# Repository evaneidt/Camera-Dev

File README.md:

# Camera-Dev
Repo for camera dev board schematics, CAD, and code.

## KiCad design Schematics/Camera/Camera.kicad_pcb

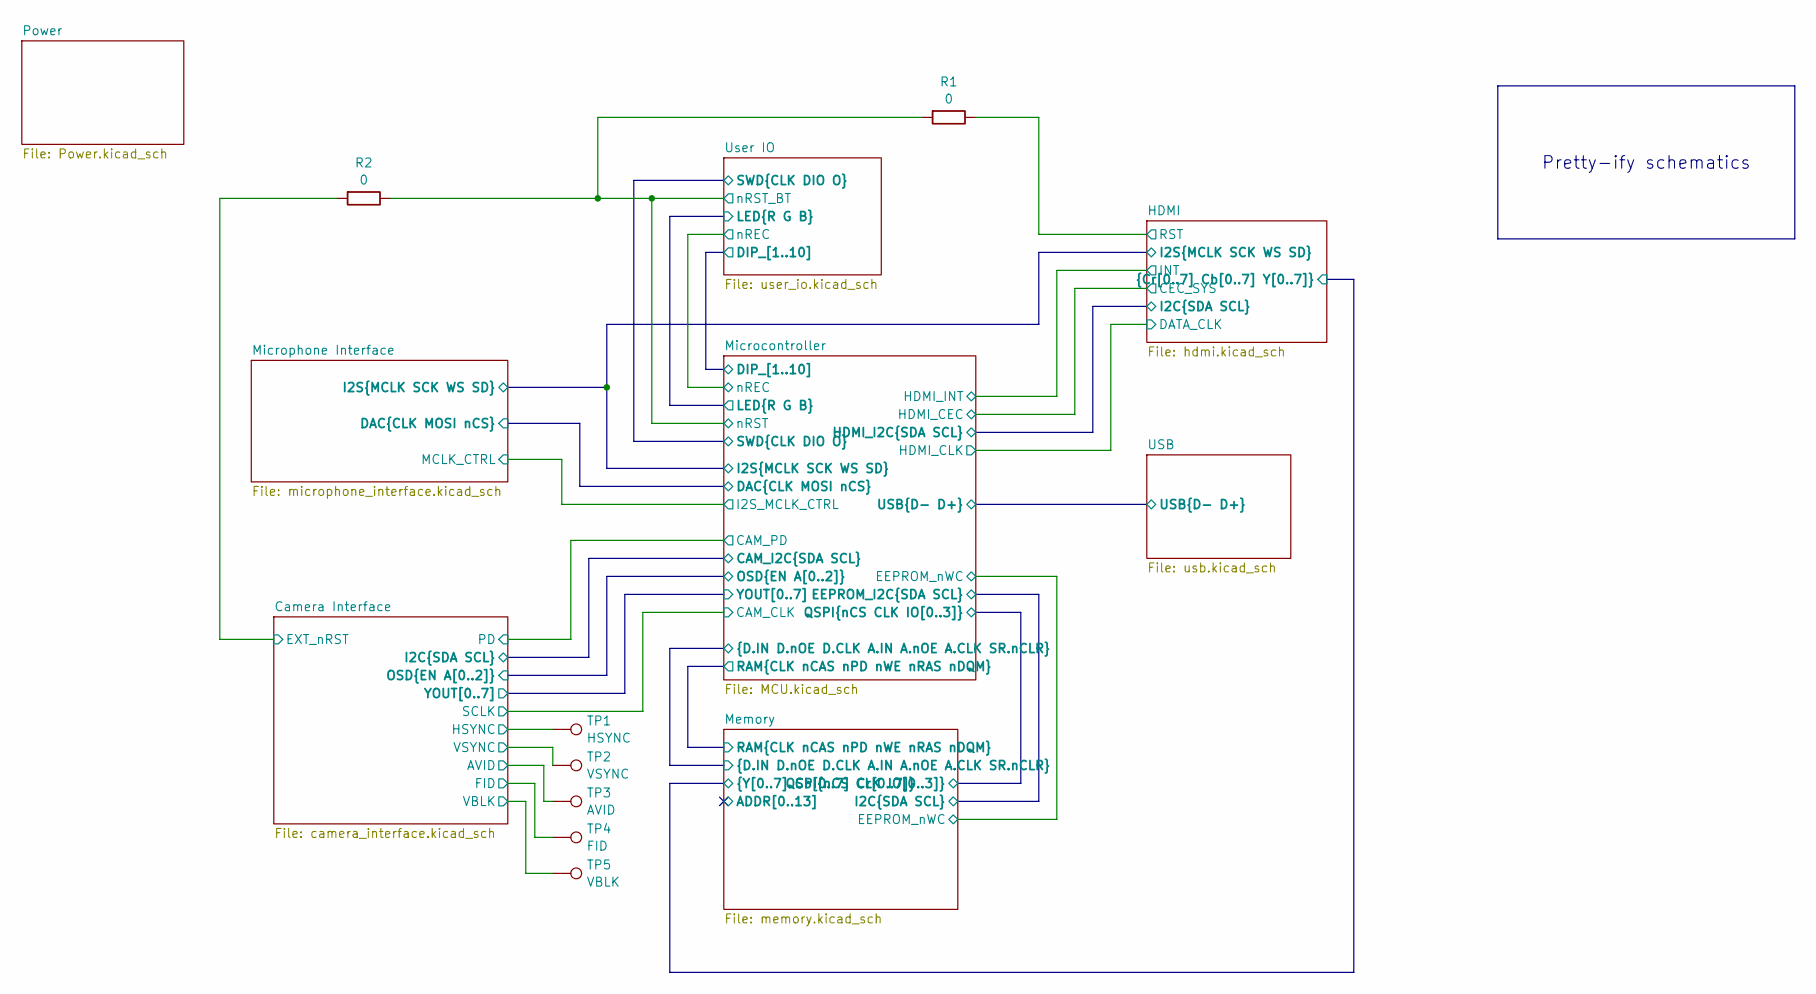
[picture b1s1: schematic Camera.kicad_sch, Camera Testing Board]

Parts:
R1, R2: 0; R_0603_1608Metric
TP1: HSYNC; TestPoint_Keystone_5000-5004_Miniature
TP2: VSYNC; TestPoint_Keystone_5000-5004_Miniature
TP3: AVID; TestPoint_Keystone_5000-5004_Miniature
TP4: FID; TestPoint_Keystone_5000-5004_Miniature
TP5: VBLK; TestPoint_Keystone_5000-5004_Miniature

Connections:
/Camera Interface/AVID: TP3.1; also elsewhere on the board
/Camera Interface/EXT_nRST: R2.1; also elsewhere on the board
/Camera Interface/FID: TP4.1; also elsewhere on the board
/Camera Interface/HSYNC: TP1.1; also elsewhere on the board
/Camera Interface/VBLK: TP5.1; also elsewhere on the board
/Camera Interface/VSYNC: TP2.1; also elsewhere on the board
/HDMI/RST: R1.2; also elsewhere on the board
/User IO/nRST_BT: R1.1, R2.2; also elsewhere on the board

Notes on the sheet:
Pretty-ify schematics

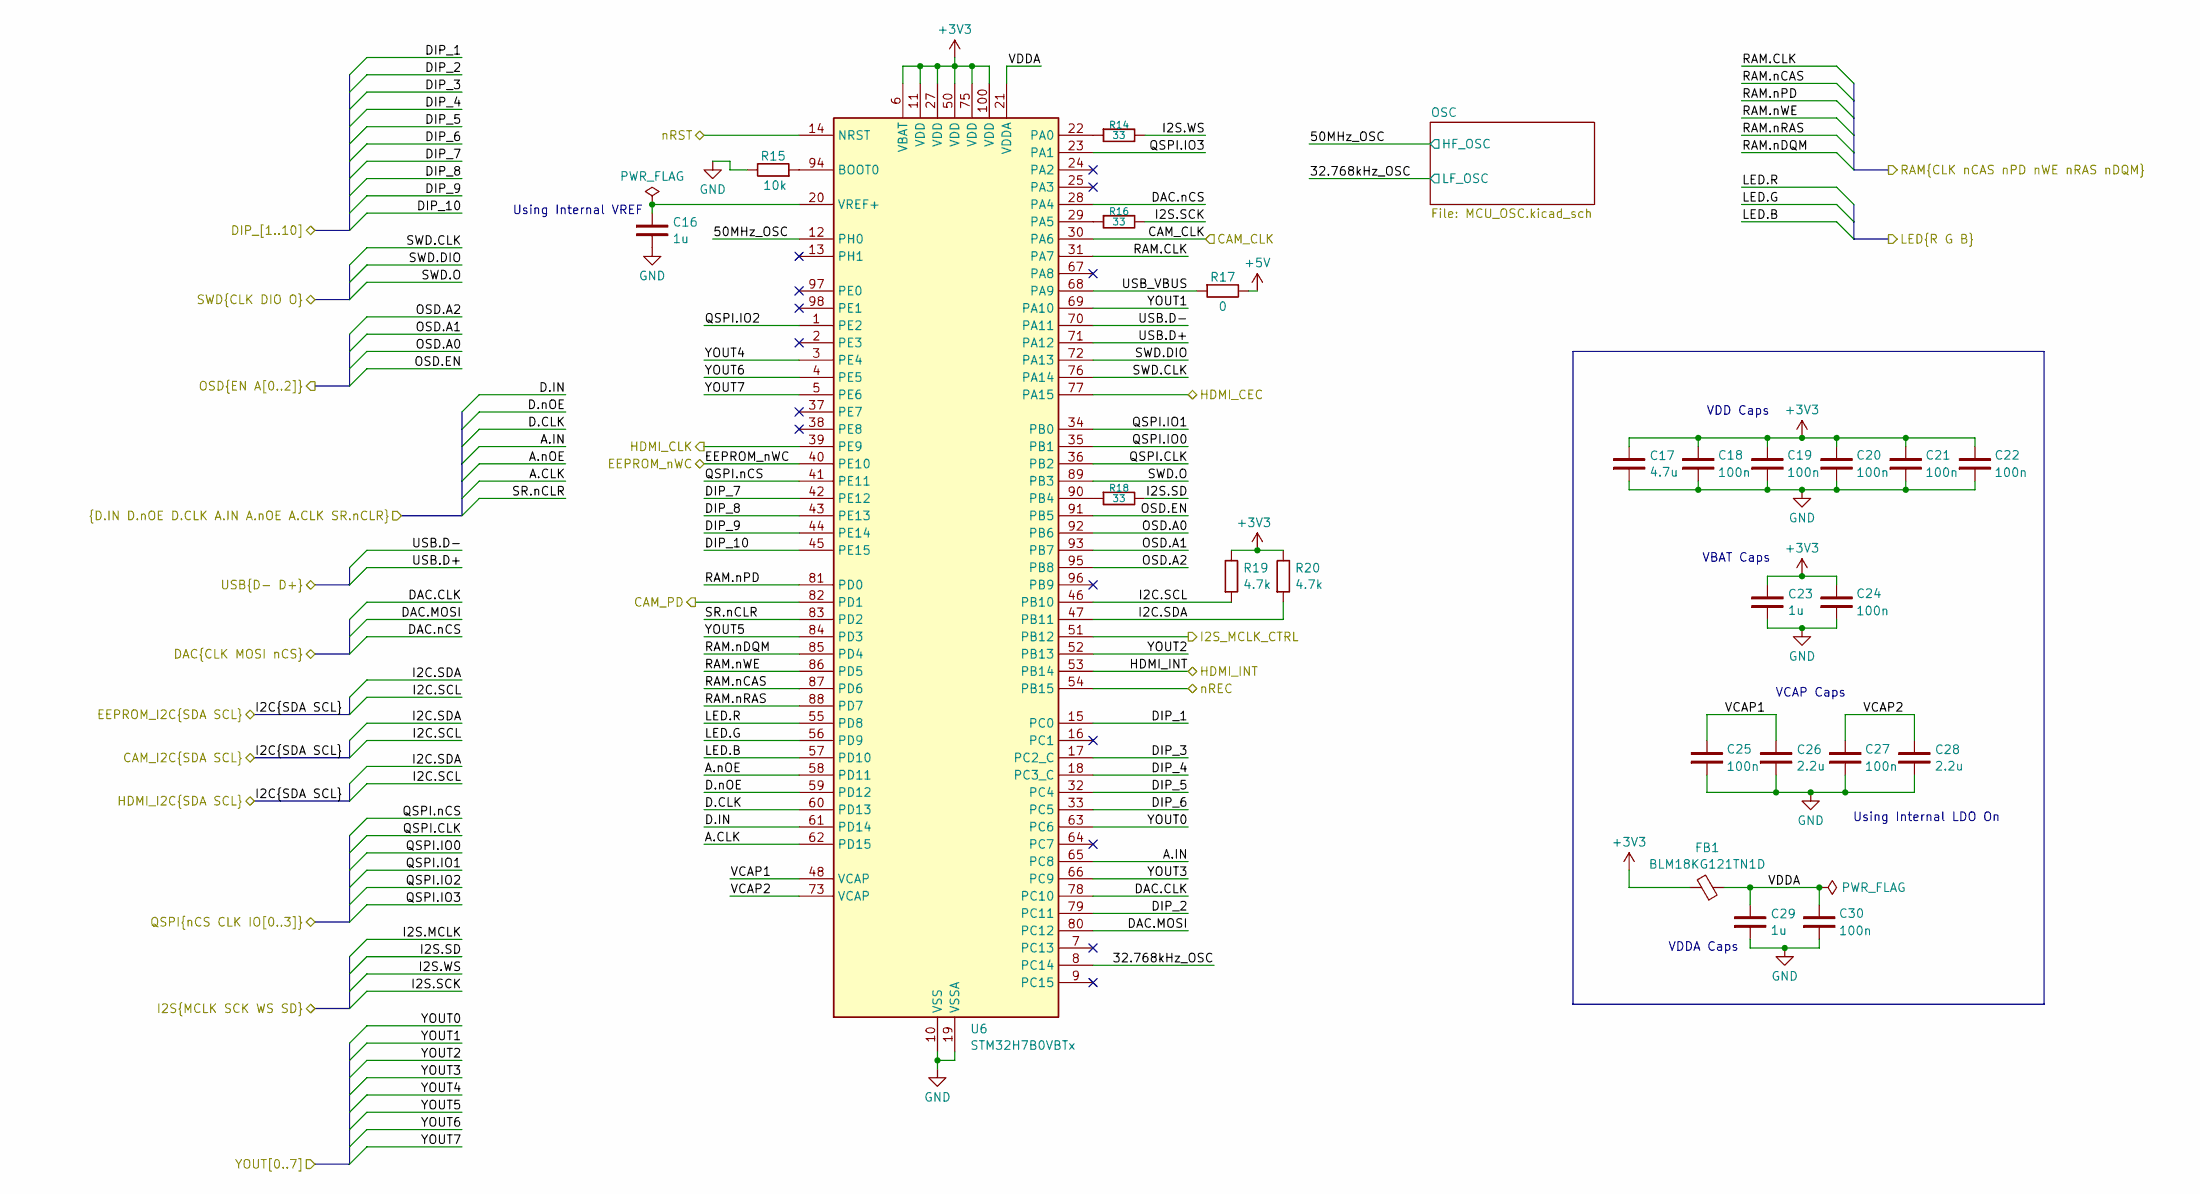
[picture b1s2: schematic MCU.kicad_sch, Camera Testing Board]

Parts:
C16, C23, C29: 1u; C_0603_1608Metric
C17: 4.7u; C_0603_1608Metric
C18, C19, C20, C21, C22, C24, C25, C27, C30: 100n; C_0603_1608Metric
C26, C28: 2.2u; C_0603_1608Metric
FB1: BLM18KG121TN1D; L_0603_1608Metric
R14, R16, R18: 33; R_0402_1005Metric
R15: 10k; R_0603_1608Metric
R17: 0; R_0603_1608Metric
R19, R20: 4.7k; R_0603_1608Metric
U6: STM32H7B0VBTx; LQFP-100_14x14mm_P0.5mm

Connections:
+3V3: C17.2, C18.2, C19.2, C20.2, C21.2, C22.2, C23.2, C24.2, FB1.2, R19.2, R20.2, U6.6 (VBAT), U6.11 (VDD), U6.27 (VDD), U6.50 (VDD), U6.75 (VDD), U6.100 (VDD); also elsewhere on the board
+5V: R17.2; also elsewhere on the board
/Camera Interface/OSD.A0: U6.92 (PB6); also elsewhere on the board
/Camera Interface/OSD.A1: U6.93 (PB7); also elsewhere on the board
/Camera Interface/OSD.A2: U6.95 (PB8); also elsewhere on the board
/Camera Interface/OSD.EN: U6.91 (PB5); also elsewhere on the board
/Camera Interface/PD: U6.82 (PD1); also elsewhere on the board
/Camera Interface/SCLK: U6.30 (PA6); also elsewhere on the board
/Camera Interface/YOUT0: U6.63 (PC6); also elsewhere on the board
/Camera Interface/YOUT1: U6.69 (PA10); also elsewhere on the board
/Camera Interface/YOUT2: U6.52 (PB13); also elsewhere on the board
/Camera Interface/YOUT3: U6.66 (PC9); also elsewhere on the board
/Camera Interface/YOUT4: U6.3 (PE4); also elsewhere on the board
/Camera Interface/YOUT5: U6.84 (PD3); also elsewhere on the board
/Camera Interface/YOUT6: U6.4 (PE5); also elsewhere on the board
/Camera Interface/YOUT7: U6.5 (PE6); also elsewhere on the board
/HDMI/CEC_SYS: U6.77 (PA15); also elsewhere on the board
/HDMI/DATA_CLK: U6.39 (PE9); also elsewhere on the board
/HDMI/I2C.SCL: R19.1, U6.46 (PB10); also elsewhere on the board
/HDMI/I2C.SDA: R20.1, U6.47 (PB11); also elsewhere on the board
/HDMI/I2S.SCK: R16.2; also elsewhere on the board
/HDMI/I2S.SD: R18.2; also elsewhere on the board
/HDMI/I2S.WS: R14.2; also elsewhere on the board
/HDMI/INT: U6.53 (PB14); also elsewhere on the board
/Memory/A.CLK: U6.62 (PD15); also elsewhere on the board
/Memory/A.IN: U6.65 (PC8); also elsewhere on the board
/Memory/A.nOE: U6.58 (PD11); also elsewhere on the board
/Memory/D.CLK: U6.60 (PD13); also elsewhere on the board
/Memory/D.IN: U6.61 (PD14); also elsewhere on the board
/Memory/D.nOE: U6.59 (PD12); also elsewhere on the board
/Memory/EEPROM_nWC: U6.40 (PE10); also elsewhere on the board
/Memory/QSPI.CLK: U6.36 (PB2); also elsewhere on the board
/Memory/QSPI.IO0: U6.35 (PB1); also elsewhere on the board
/Memory/QSPI.IO1: U6.34 (PB0); also elsewhere on the board
/Memory/QSPI.IO2: U6.1 (PE2); also elsewhere on the board
/Memory/QSPI.IO3: U6.23 (PA1); also elsewhere on the board
/Memory/QSPI.nCS: U6.41 (PE11); also elsewhere on the board
/Memory/RAM.CLK: U6.31 (PA7); also elsewhere on the board
/Memory/RAM.nCAS: U6.87 (PD6); also elsewhere on the board
/Memory/RAM.nDQM: U6.85 (PD4); also elsewhere on the board
/Memory/RAM.nPD: U6.81 (PD0); also elsewhere on the board
/Memory/RAM.nRAS: U6.88 (PD7); also elsewhere on the board
/Memory/RAM.nWE: U6.86 (PD5); also elsewhere on the board
/Memory/SR.nCLR: U6.83 (PD2); also elsewhere on the board
/Microcontroller/32.768kHz_OSC: U6.8 (PC14); also elsewhere on the board
/Microcontroller/50MHz_OSC: U6.12 (PH0); also elsewhere on the board
/Microcontroller/DAC.CLK: U6.78 (PC10); also elsewhere on the board
/Microcontroller/DAC.MOSI: U6.80 (PC12); also elsewhere on the board
/Microcontroller/DAC.nCS: U6.28 (PA4); also elsewhere on the board
/Microcontroller/DIP_1: U6.15 (PC0)
/Microcontroller/DIP_2: U6.79 (PC11)
/Microcontroller/DIP_3: U6.17 (PC2_C)
/Microcontroller/DIP_4: U6.18 (PC3_C)
/Microcontroller/DIP_5: U6.32 (PC4)
/Microcontroller/DIP_6: U6.33 (PC5)
/Microcontroller/DIP_7: U6.42 (PE12)
/Microcontroller/DIP_8: U6.43 (PE13)
/Microcontroller/DIP_9: U6.44 (PE14)
/Microcontroller/DIP_10: U6.45 (PE15)
/Microcontroller/LED.B: U6.57 (PD10); also elsewhere on the board
/Microcontroller/LED.G: U6.56 (PD9); also elsewhere on the board
/Microcontroller/LED.R: U6.55 (PD8); also elsewhere on the board
/Microcontroller/SWD.CLK: U6.76 (PA14); also elsewhere on the board
/Microcontroller/SWD.DIO: U6.72 (PA13); also elsewhere on the board
/Microcontroller/SWD.O: U6.89 (PB3); also elsewhere on the board
/Microcontroller/USB.D+: U6.71 (PA12); also elsewhere on the board
/Microcontroller/USB.D-: U6.70 (PA11); also elsewhere on the board
/Microcontroller/USB_VBUS: R17.1, U6.68 (PA9)
/Microcontroller/VCAP1: C25.2, C26.2, U6.48 (VCAP)
/Microcontroller/VCAP2: C27.2, C28.2, U6.73 (VCAP)
/Microcontroller/VDDA: C29.2, C30.2, FB1.1, U6.21 (VDDA)
/Microcontroller/nREC: U6.54 (PB15); also elsewhere on the board
/Microphone Interface/Microphone Clocks/CTRL: U6.51 (PB12); also elsewhere on the board
/User IO/nRST_BT: U6.14 (NRST); also elsewhere on the board
GND: C16.1, C17.1, C18.1, C19.1, C20.1, C21.1, C22.1, C23.1, C24.1, C25.1, C26.1, C27.1, C28.1, C29.1, C30.1, R15.2, U6.10 (VSS), U6.19 (VSSA), U6.26 (VSS), U6.49 (VSS), U6.74 (VSS), U6.99 (VSS); also elsewhere on the board
unnamed: R15.1, U6.94 (BOOT0)
unnamed: R14.1, U6.22 (PA0)
unnamed: R16.1, U6.29 (PA5)
unnamed: R18.1, U6.90 (PB4)
unnamed: C16.2, U6.20 (VREF+)

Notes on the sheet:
Using Internal LDO On
VDDA Caps
Using Internal VREF
VBAT Caps
VCAP Caps
VDD Caps

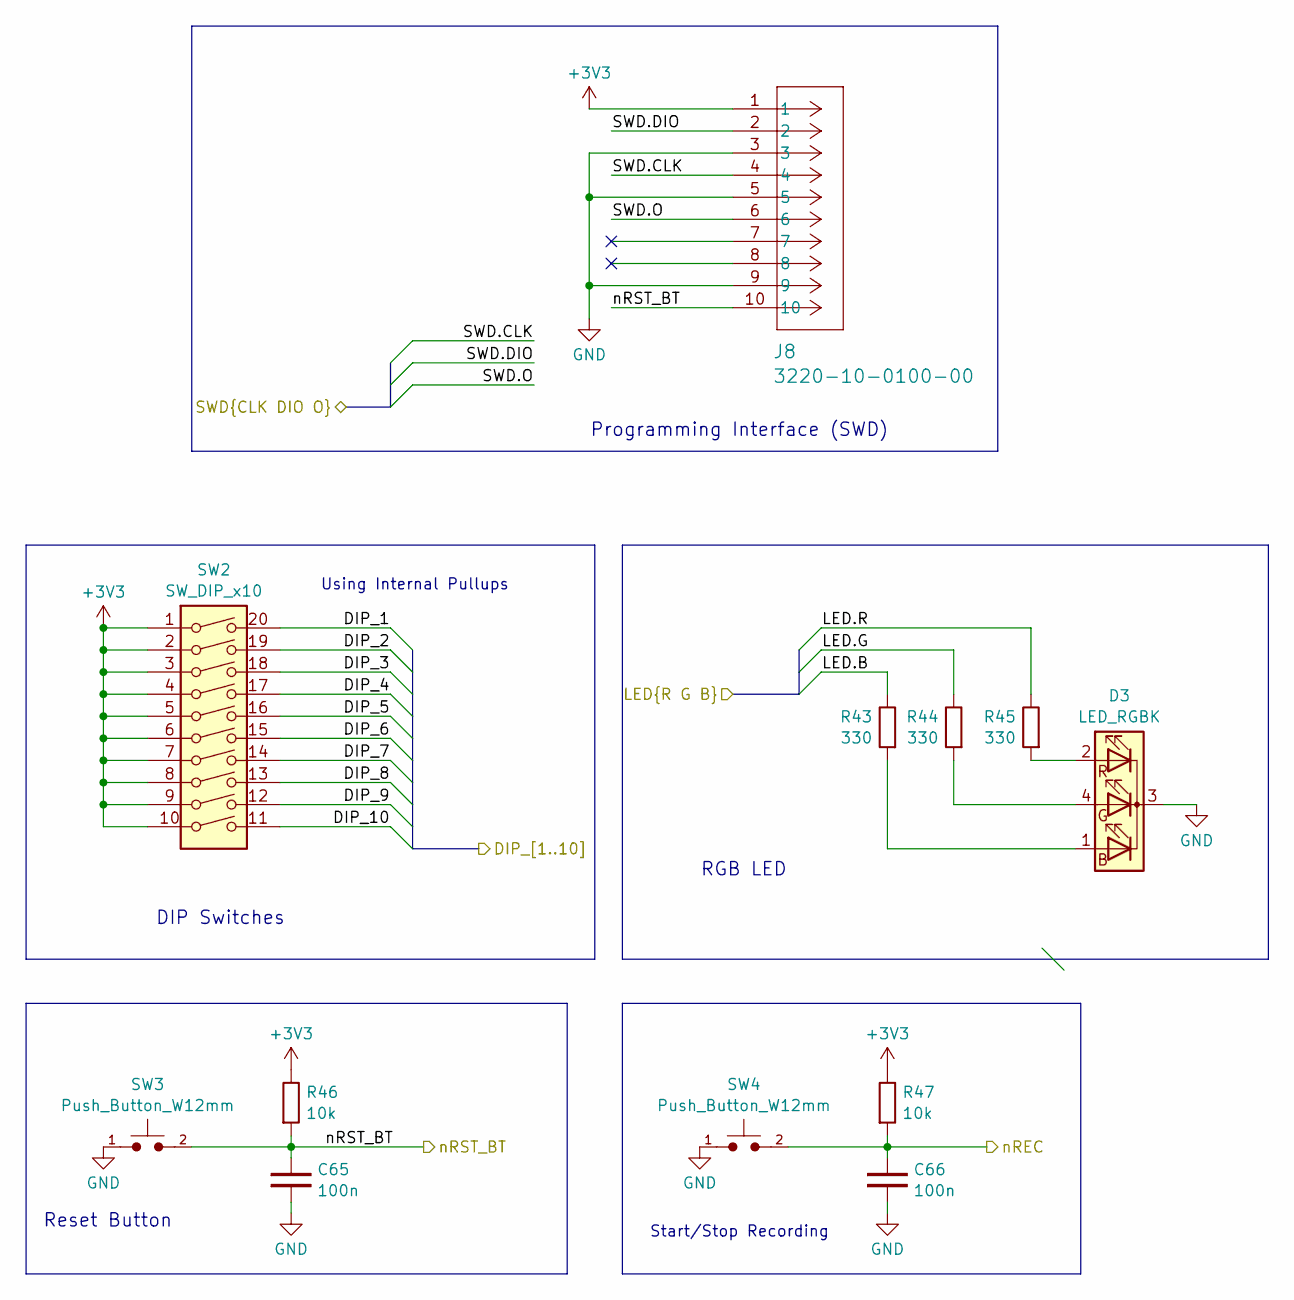
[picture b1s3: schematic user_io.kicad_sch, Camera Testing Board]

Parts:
C65, C66: 100n; C_0603_1608Metric
D3: LED_RGBK; LED_D5.0mm-4_RGB
J8: 3220-10-0100-00; CONN_3220-10-0100-00_CNC
R43, R44, R45: 330; R_0603_1608Metric
R46, R47: 10k; R_0603_1608Metric
SW2: SW_DIP_x10; DIP-20_W7.62mm
SW3, SW4: Push_Button_W12mm; SW_Push_1P1T_NO_CK_KSC7xxJ

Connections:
+3V3: J8.1, R46.2, R47.2, SW2.1, SW2.2, SW2.3, SW2.4, SW2.5, SW2.6, SW2.7, SW2.8, SW2.9, SW2.10; also elsewhere on the board
/Microcontroller/LED.B: R43.2; also elsewhere on the board
/Microcontroller/LED.G: R44.2; also elsewhere on the board
/Microcontroller/LED.R: R45.2; also elsewhere on the board
/Microcontroller/SWD.CLK: J8.4; also elsewhere on the board
/Microcontroller/SWD.DIO: J8.2; also elsewhere on the board
/Microcontroller/SWD.O: J8.6; also elsewhere on the board
/Microcontroller/nREC: C66.2, R47.1, SW4.2; also elsewhere on the board
/User IO/nRST_BT: C65.2, J8.10, R46.1, SW3.2; also elsewhere on the board
GND: C65.1, C66.1, D3.3 (K), J8.3, J8.5, J8.9, SW3.1, SW4.1; also elsewhere on the board
unnamed: D3.1 (BA), R43.1
unnamed: D3.4 (GA), R44.1
unnamed: D3.2 (RA), R45.1

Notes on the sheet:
Using Internal Pullups
DIP Switches
Programming Interface (SWD)
Start/Stop Recording
Reset Button
RGB LED

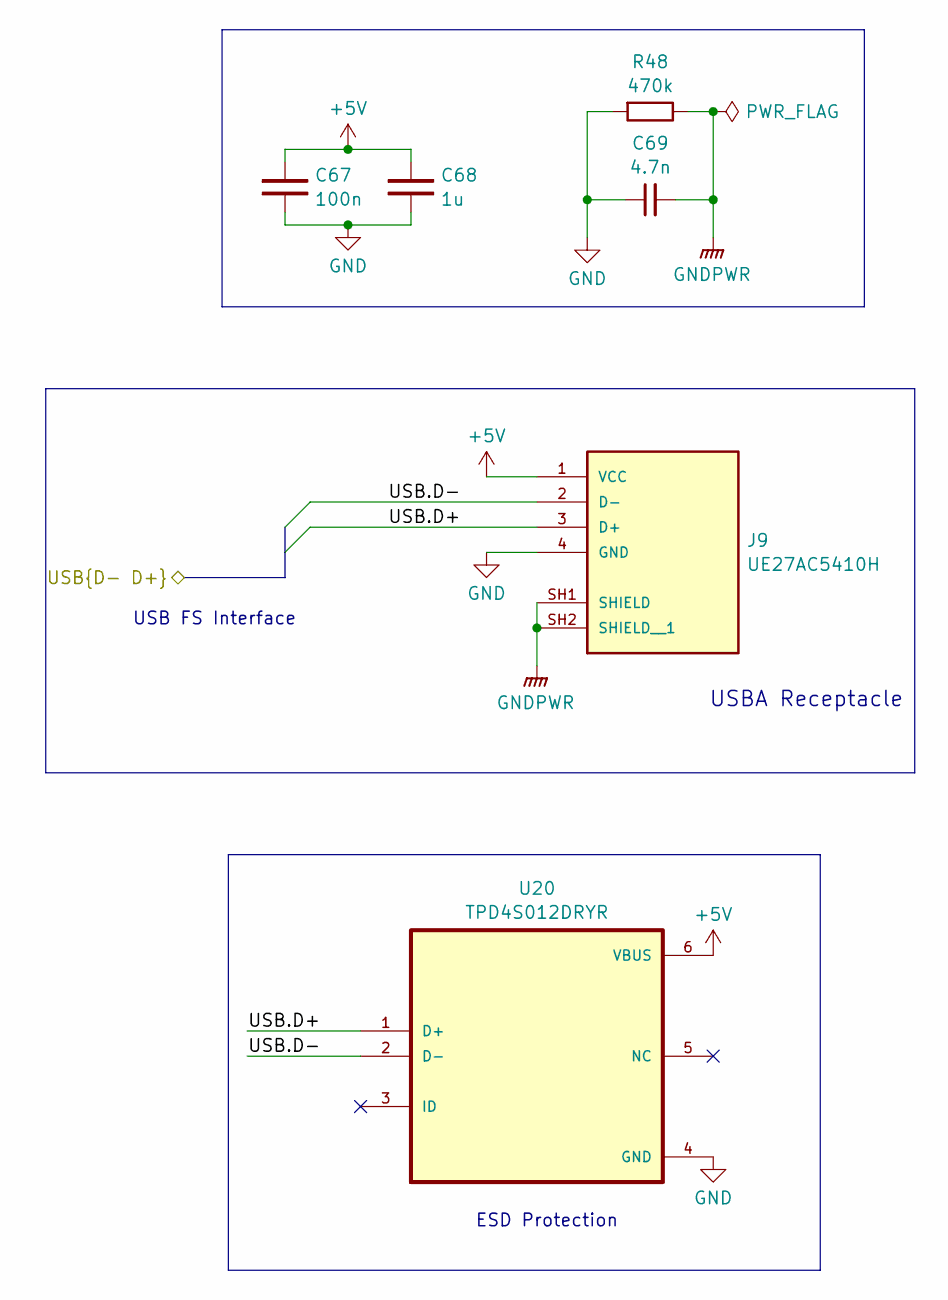
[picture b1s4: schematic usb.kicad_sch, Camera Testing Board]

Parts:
C67: 100n; C_0603_1608Metric
C68: 1u; C_0603_1608Metric
C69: 4.7n; C_0603_1608Metric
J9: UE27AC5410H; AMPHENOL_UE27AC5410H; PARTREV G
R48: 470k; R_0603_1608Metric
U20: TPD4S012DRYR; PSON50P145X100X60-6N

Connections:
+5V: C67.2, C68.2, J9.1 (VCC), U20.6 (VBUS); also elsewhere on the board
/Microcontroller/USB.D+: J9.3 (D+), U20.1 (D+); also elsewhere on the board
/Microcontroller/USB.D-: J9.2 (D-), U20.2 (D-); also elsewhere on the board
GND: C67.1, C68.1, C69.1, J9.4 (GND), R48.1, U20.4 (GND); also elsewhere on the board
GNDPWR: C69.2, J9.SH1 (SHIELD), J9.SH2 (SHIELD__1), R48.2; also elsewhere on the board

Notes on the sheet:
USB FS Interface
ESD Protection
USBA Receptacle

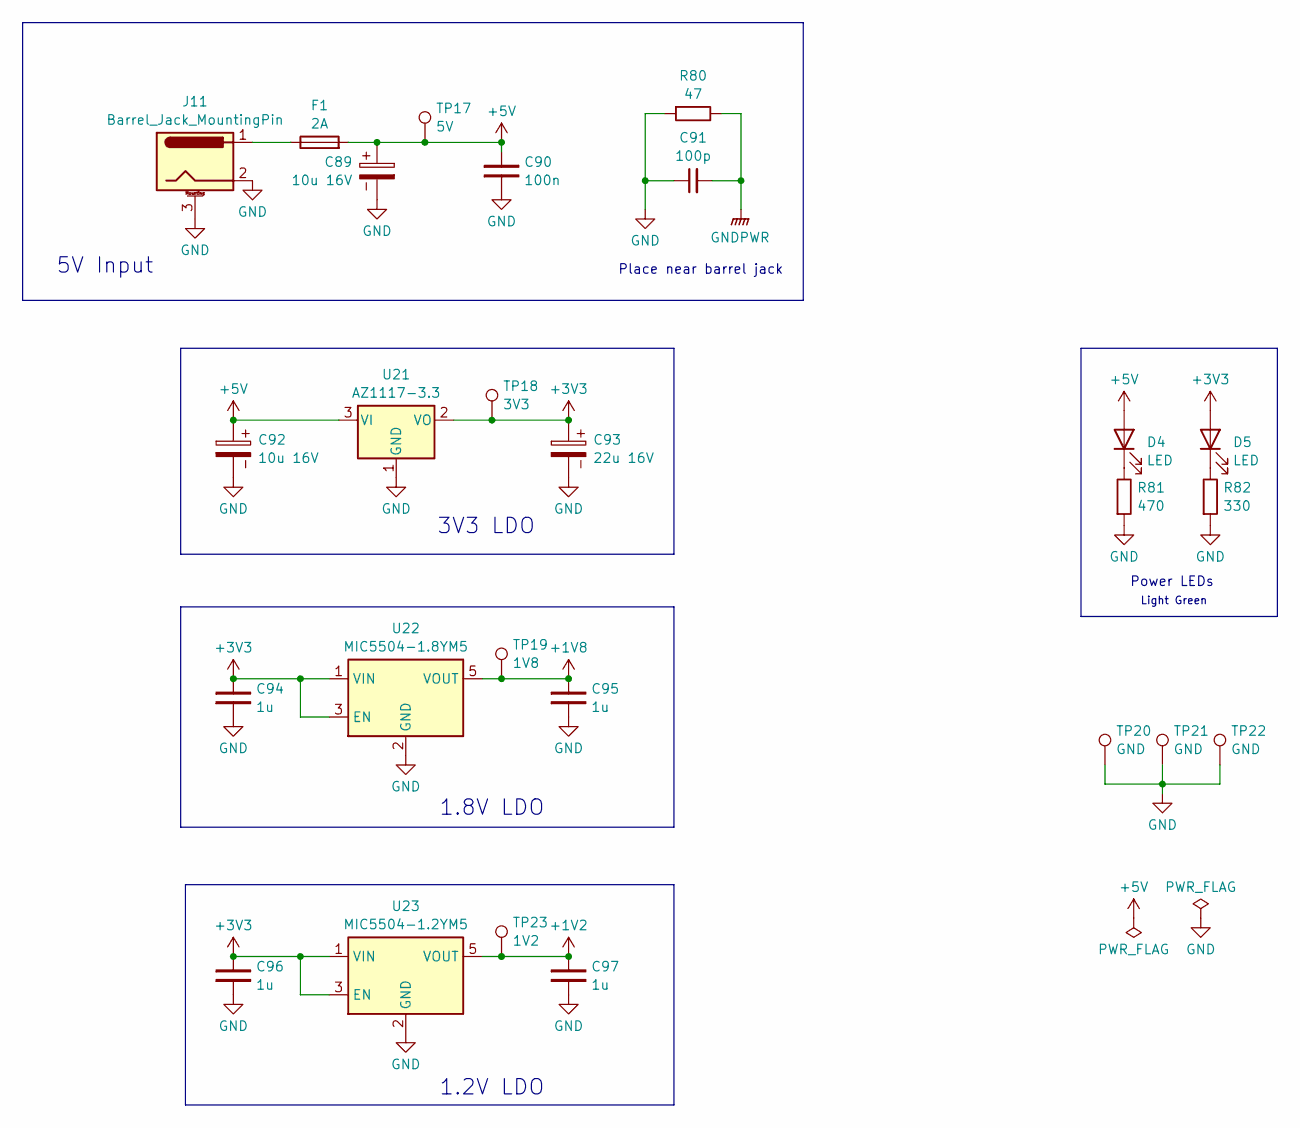
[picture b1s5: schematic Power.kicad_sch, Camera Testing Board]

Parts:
C89, C92: 10u 16V; CP_EIA-3216-18_Kemet-A
C90: 100n; C_0603_1608Metric
C91: 100p; C_0402_1005Metric
C93: 22u 16V; CP_EIA-3528-21_Kemet-B
C94, C95, C96, C97: 1u; C_0603_1608Metric
D4, D5: LED; LED_0603_1608Metric
F1: 2A; Fuse_0603_1608Metric_Pad1.05x0.95mm_HandSolder
J11: Barrel_Jack_MountingPin; BarrelJack_CUI_PJ-036AH-SMT_Horizontal
R80: 47; R_0603_1608Metric
R81: 470; R_0603_1608Metric
R82: 330; R_0603_1608Metric
TP17: 5V; TestPoint_Keystone_5000-5004_Miniature
TP18: 3V3; TestPoint_Keystone_5000-5004_Miniature
TP19: 1V8; TestPoint_Keystone_5000-5004_Miniature
TP20, TP21, TP22: GND; TestPoint_Keystone_5010-5014_Multipurpose
TP23: 1V2; TestPoint_Keystone_5000-5004_Miniature
U21: AZ1117-3.3; SOT-223-3_TabPin2
U22: MIC5504-1.8YM5; SOT-23-5
U23: MIC5504-1.2YM5; SOT-23-5

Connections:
+1V2: C97.2, TP23.1, U23.5 (VOUT); also elsewhere on the board
+1V8: C95.2, TP19.1, U22.5 (VOUT); also elsewhere on the board
+3V3: C93.1, C94.2, C96.2, D5.2 (A), TP18.1, U21.2 (VO), U22.1 (VIN), U22.3 (EN), U23.1 (VIN), U23.3 (EN); also elsewhere on the board
+5V: C89.1, C90.2, C92.1, D4.2 (A), F1.2, TP17.1, U21.3 (VI); also elsewhere on the board
GND: C89.2, C90.1, C91.1, C92.2, C93.2, C94.1, C95.1, C96.1, C97.1, J11.2, J11.3 (MountPin), R80.1, R81.1, R82.1, TP20.1, TP21.1, TP22.1, U21.1 (GND), U22.2 (GND), U23.2 (GND); also elsewhere on the board
GNDPWR: C91.2, R80.2; also elsewhere on the board
unnamed: D4.1 (K), R81.2
unnamed: D5.1 (K), R82.2
unnamed: F1.1, J11.1

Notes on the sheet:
Place near barrel jack
1.8V LDO
1.2V LDO
Power LEDs
3V3 LDO
Light Green
5V Input

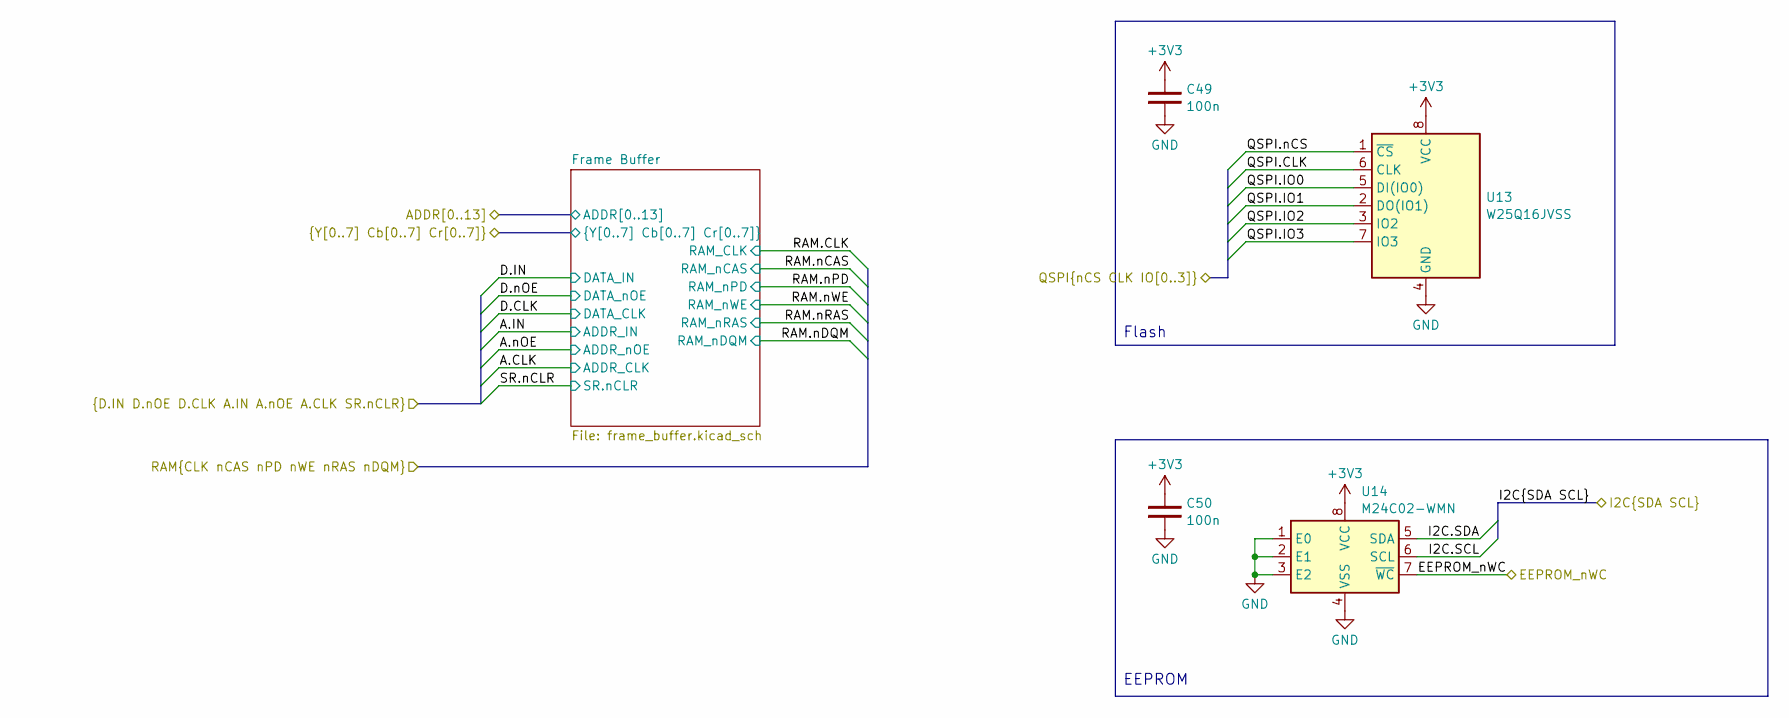
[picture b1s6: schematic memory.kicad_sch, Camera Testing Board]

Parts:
C49, C50: 100n; C_0603_1608Metric
U13: W25Q16JVSS; SOIC-8_5.23x5.23mm_P1.27mm
U14: M24C02-WMN; SOIC-8_3.9x4.9mm_P1.27mm

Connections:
+3V3: C49.2, C50.2, U13.8 (VCC), U14.8 (VCC); also elsewhere on the board
/HDMI/I2C.SCL: U14.6 (SCL); also elsewhere on the board
/HDMI/I2C.SDA: U14.5 (SDA); also elsewhere on the board
/Memory/EEPROM_nWC: U14.7 (~WC); also elsewhere on the board
/Memory/QSPI.CLK: U13.6 (CLK); also elsewhere on the board
/Memory/QSPI.IO0: U13.5 (DI(IO0)); also elsewhere on the board
/Memory/QSPI.IO1: U13.2 (DO(IO1)); also elsewhere on the board
/Memory/QSPI.IO2: U13.3 (IO2); also elsewhere on the board
/Memory/QSPI.IO3: U13.7 (IO3); also elsewhere on the board
/Memory/QSPI.nCS: U13.1 (~CS); also elsewhere on the board
GND: C49.1, C50.1, U13.4 (GND), U14.1 (E0), U14.2 (E1), U14.3 (E2), U14.4 (VSS); also elsewhere on the board

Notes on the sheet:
Flash
EEPROM

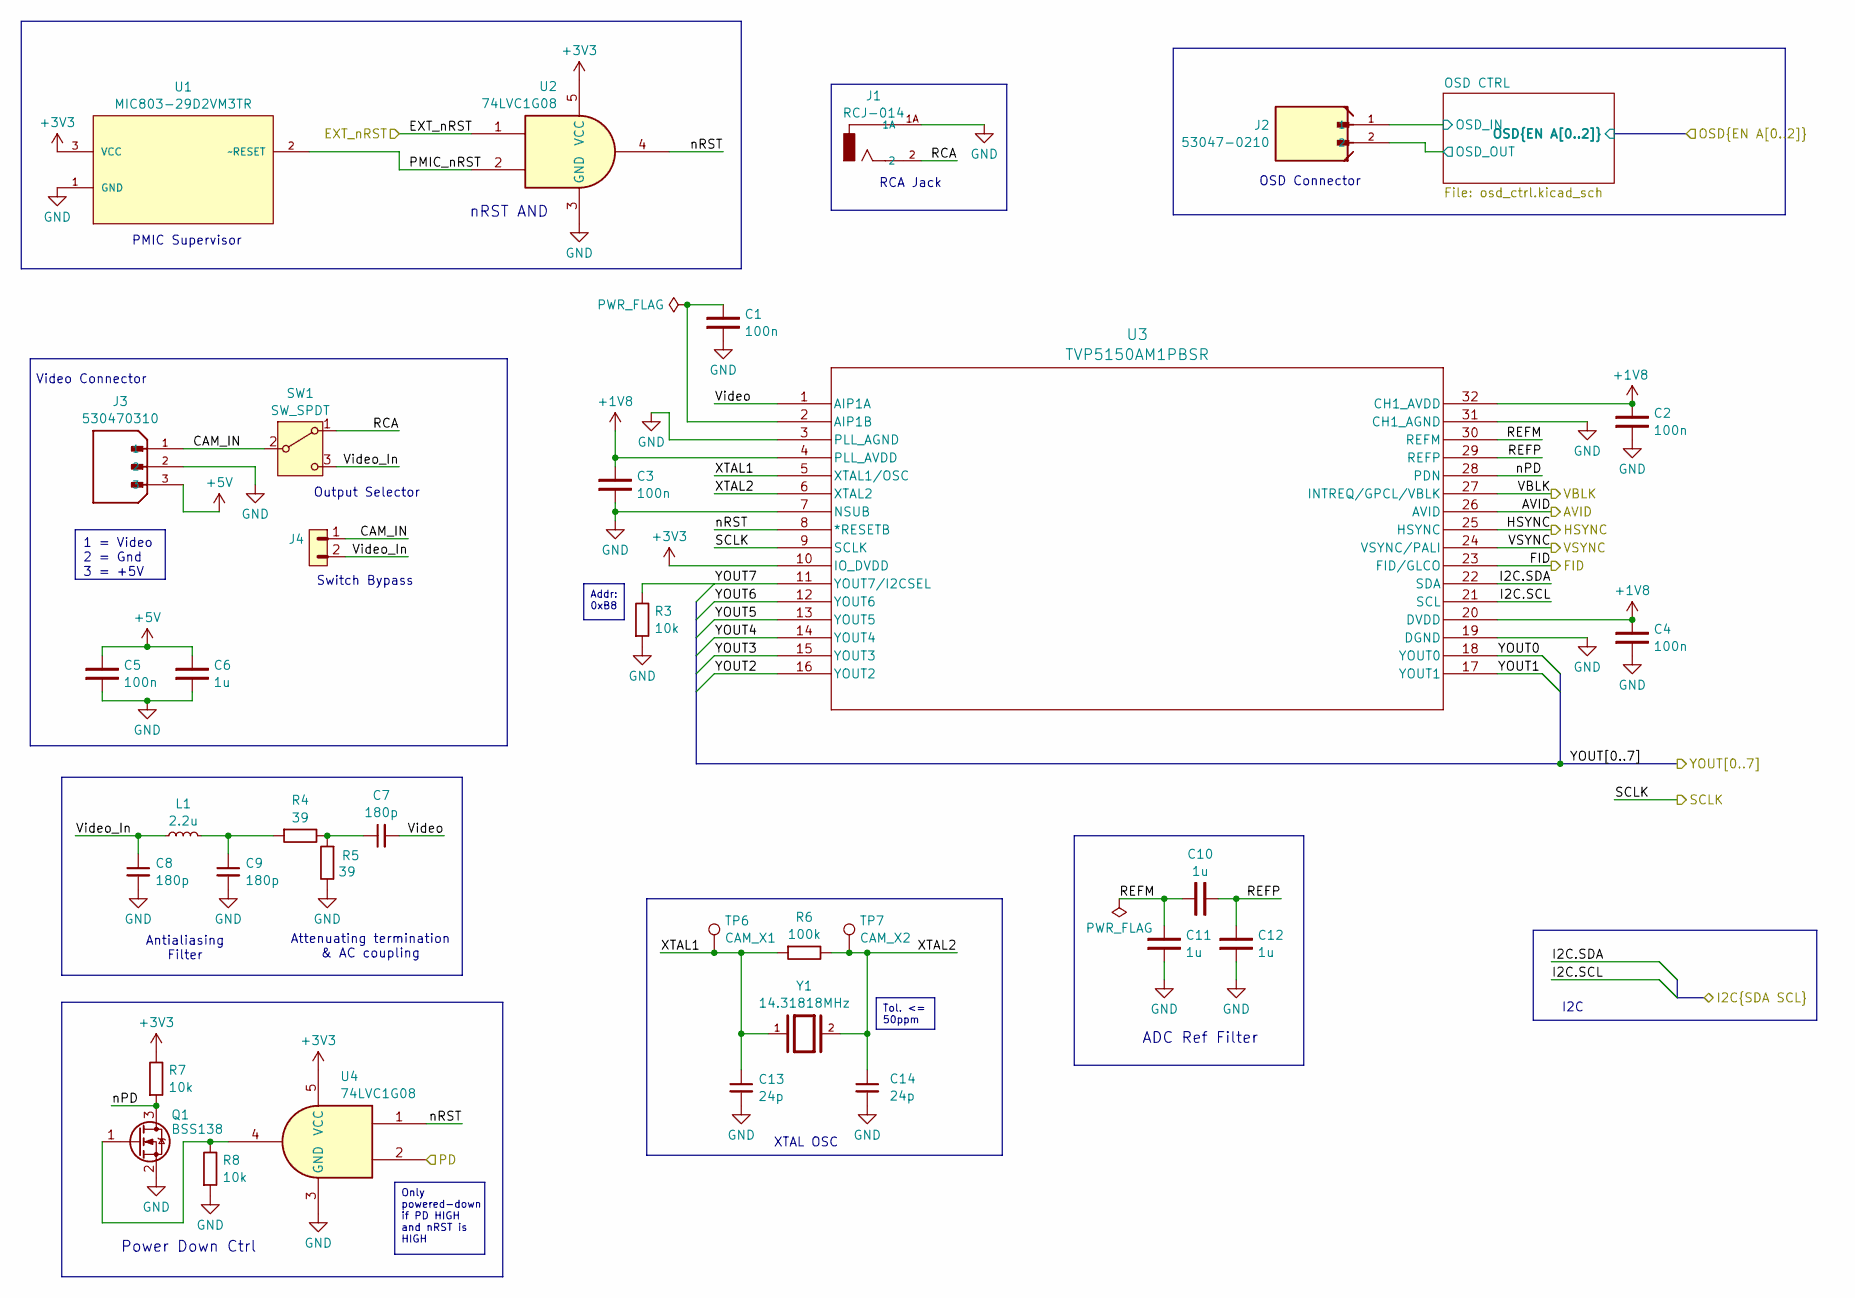
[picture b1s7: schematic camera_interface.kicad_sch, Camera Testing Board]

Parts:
C1, C2, C3, C4, C5: 100n; C_0603_1608Metric
C6, C10, C11, C12: 1u; C_0603_1608Metric
C7, C8, C9: 180p; C_0402_1005Metric
C13, C14: 24p; C_0402_1005Metric
J1: RCJ-014; CUI_RCJ-014; PART_REV B
J2: 53047-0210; Molex_PicoBlade_53047-0210_1x02_P1.25mm_Vertical; PARTREV 04/19/2022
J3: 530470310; MOLEX_530470310; PARTREV A
J4: PINHD_1x2_Male; PinHeader_1x02_P2.54mm_Vertical
L1: 2.2u; L_1008_2520Metric
Q1: BSS138; SOT-23
R3, R7, R8: 10k; R_0603_1608Metric
R4, R5: 39; R_0603_1608Metric
R6: 100k; R_0603_1608Metric
SW1: SW_SPDT; SW_Slide_SPDT_Straight_CK_OS102011MS2Q
TP6: CAM_X1; TestPoint_Keystone_5000-5004_Miniature
TP7: CAM_X2; TestPoint_Keystone_5000-5004_Miniature
U1: MIC803-29D2VM3TR; SOT95P232X110-3N; MPN MIC803-29D2VM3TR
U2, U4: 74LVC1G08; SOT-23-5
U3: TVP5150AM1PBSR; PBS32
Y1: 14.31818MHz; XTAL_ABLS2-14.31818MHZ-D4Y-T; PARTREV 11.15.2016

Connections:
+1V8: C2.2, C3.2, C4.2, U3.4 (PLL_AVDD), U3.20 (DVDD), U3.32 (CH1_AVDD); also elsewhere on the board
+3V3: R7.2, U1.3 (VCC), U2.5 (VCC), U3.10 (IO_DVDD), U4.5 (VCC); also elsewhere on the board
+5V: C5.2, C6.2, J3.3; also elsewhere on the board
/Camera Interface/AVID: U3.26 (AVID); also elsewhere on the board
/Camera Interface/CAM_IN: J3.1, J4.1, SW1.2 (B)
/Camera Interface/EXT_nRST: U2.1; also elsewhere on the board
/Camera Interface/FID: U3.23 (FID/GLCO); also elsewhere on the board
/Camera Interface/HSYNC: U3.25 (HSYNC); also elsewhere on the board
/Camera Interface/OSD CTRL/OSD_IN: J2.1; also elsewhere on the board
/Camera Interface/OSD CTRL/OSD_OUT: J2.2; also elsewhere on the board
/Camera Interface/PD: U4.2; also elsewhere on the board
/Camera Interface/PMIC_nRST: U1.2 (~RESET), U2.2
/Camera Interface/RCA: J1.2, SW1.1 (A)
/Camera Interface/REFM: C10.2, C11.2, U3.30 (REFM)
/Camera Interface/REFP: C10.1, C12.2, U3.29 (REFP)
/Camera Interface/SCLK: U3.9 (SCLK); also elsewhere on the board
/Camera Interface/VBLK: U3.27 (INTREQ/GPCL/VBLK); also elsewhere on the board
/Camera Interface/VSYNC: U3.24 (VSYNC/PALI); also elsewhere on the board
/Camera Interface/Video: C7.2, U3.1 (AIP1A)
/Camera Interface/Video_In: C8.1, J4.2, L1.1, SW1.3 (C)
/Camera Interface/XTAL1: C13.1, R6.1, TP6.1, U3.5 (XTAL1/OSC), Y1.1
/Camera Interface/XTAL2: C14.1, R6.2, TP7.1, U3.6 (XTAL2), Y1.2
/Camera Interface/YOUT0: U3.18 (YOUT0); also elsewhere on the board
/Camera Interface/YOUT1: U3.17 (YOUT1); also elsewhere on the board
/Camera Interface/YOUT2: U3.16 (YOUT2); also elsewhere on the board
/Camera Interface/YOUT3: U3.15 (YOUT3); also elsewhere on the board
/Camera Interface/YOUT4: U3.14 (YOUT4); also elsewhere on the board
/Camera Interface/YOUT5: U3.13 (YOUT5); also elsewhere on the board
/Camera Interface/YOUT6: U3.12 (YOUT6); also elsewhere on the board
/Camera Interface/YOUT7: R3.2, U3.11 (YOUT7/I2CSEL); also elsewhere on the board
/Camera Interface/nPD: Q1.3 (D), R7.1, U3.28 (PDN)
/Camera Interface/nRST: U2.4, U3.8 (*RESETB), U4.1
/HDMI/I2C.SCL: U3.21 (SCL); also elsewhere on the board
/HDMI/I2C.SDA: U3.22 (SDA); also elsewhere on the board
GND: C1.1, C2.1, C3.1, C4.1, C5.1, C6.1, C8.2, C9.2, C11.1, C12.1, C13.2, C14.2, J1.1A, J3.2, Q1.2 (S), R3.1, R5.2, R8.1, U1.1 (GND), U2.3 (GND), U3.3 (PLL_AGND), U3.7 (NSUB), U3.19 (DGND), U3.31 (CH1_AGND), U4.3 (GND); also elsewhere on the board
unnamed: C7.1, R4.2, R5.1
unnamed: C9.1, L1.2, R4.1
unnamed: Q1.1 (G), R8.2, U4.4
unnamed: C1.2, U3.2 (AIP1B)

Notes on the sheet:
Addr: 0xB8
Only powered-down if PD HIGH and nRST is HIGH
Tol. <= 50ppm
1 = Video 2 = Gnd 3 = +5V
I2C
Switch Bypass
PMIC Supervisor
Power Down Ctrl
Attenuating termination & AC coupling
XTAL OSC
OSD Connector
nRST AND
Video Connector
Antialiasing Filter
ADC Ref Filter
RCA Jack
Output Selector
